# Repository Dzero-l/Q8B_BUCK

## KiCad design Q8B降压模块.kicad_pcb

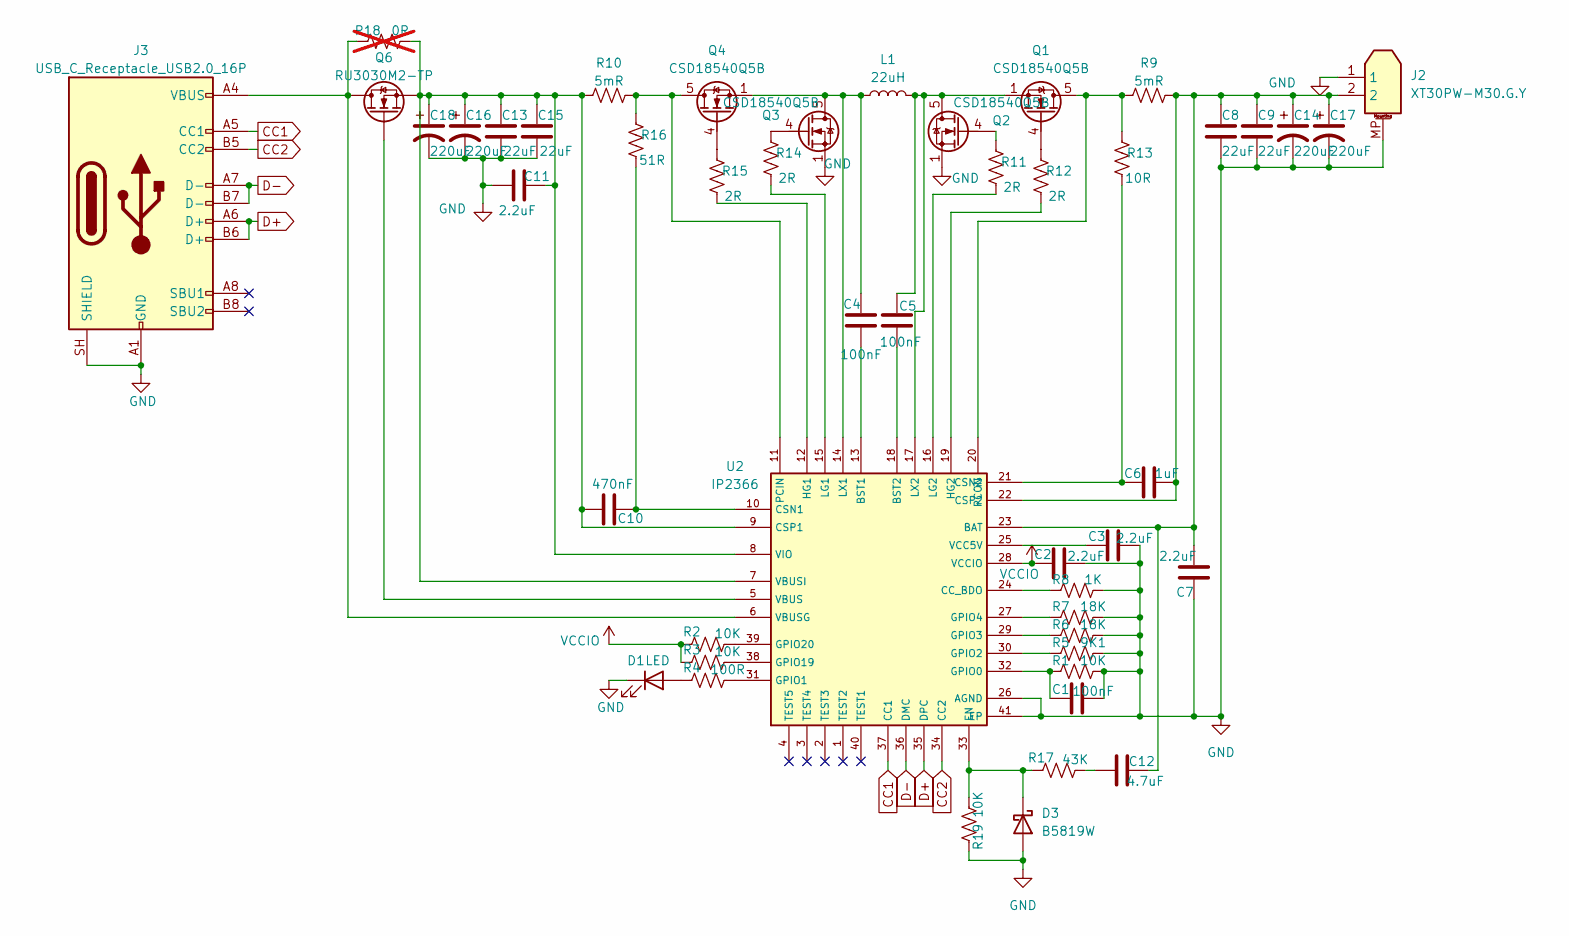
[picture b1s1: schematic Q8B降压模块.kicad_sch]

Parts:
C1, C4, C5: 100nF; C_0603_1608Metric
C2, C3, C7, C11: 2.2uF; C_0603_1608Metric
C6: 1uF; C_0603_1608Metric
C8, C9, C13, C15: 22uF; C_1206_3216Metric
C10: 470nF; C_0603_1608Metric
C12: 4.7uF; C_0805_2012Metric
C14, C16, C17, C18: 220uF; CP_Radial_D8.0mm_P3.50mm
D1: LED; LED_0603_1608Metric
D3: B5819W; D_SOD-123
J2: XT30PW-M30.G.Y; AMASS_XT30PW_M30_G_Y
J3: USB_C_Receptacle_USB2.0_16P; USB_C_Receptacle_GCT_USB4105-xx-A_16P_TopMnt_Horizontal
L1: 22uH; L_APV_APH1770
Q1, Q2, Q3, Q4: CSD18540Q5B; TDSON-8_L5.9-W5.2-P1.27_TPCA8122-Toshiba
Q6: RU3030M2-TP; MPN RU3030M2-TP
R1, R2, R3, R19: 10K; R_0603_1608Metric
R4: 100R; R_0603_1608Metric
R5: 9K1; R_0603_1608Metric
R6, R7: 18K; R_0603_1608Metric
R8: 1K; R_0603_1608Metric
R9, R10: 5mR; R_0612_1632Metric
R11, R12, R14, R15: 2R; R_0603_1608Metric
R13: 10R; R_0603_1608Metric
R16: 51R; R_0603_1608Metric
R17: 43K; R_0603_1608Metric
R18: 0R; C_1206_3216Metric; not fitted
U2: IP2366; QFN-40-5x5mm_P0.4mm_EP3.7mm

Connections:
CC1: J3.A5 (CC1), U2.37 (CC1)
CC2: J3.B5 (CC2), U2.34 (CC2)
D+: J3.A6 (D+), J3.B6 (D+), U2.35 (DPC)
D-: J3.A7 (D-), J3.B7 (D-), U2.36 (DMC)
GND: C1.2, C2.2, C3.2, C7.1, C8.2, C9.2, C11.1, C13.2, C14.2, C15.2, C16.2, C17.2, C18.2, D1.1 (K), D3.2 (A), J2.1, J2.MP, J3.A1 (GND), J3.A12 (GND), J3.B1 (GND), J3.B12 (GND), J3.SH (SHIELD), Q2.1 (S), Q2.2 (S), Q2.3 (S), Q3.1 (S), Q3.2 (S), Q3.3 (S), R1.2, R5.2, R6.2, R7.2, R8.2, R19.1, U2.26 (AGND), U2.41 (EP)
unnamed: C12.1, R17.2
unnamed: D1.2 (A), R4.1
unnamed: D3.1 (K), R17.1, R19.2, U2.33 (EN)
unnamed: Q1.5 (D), R9.1, R13.1, U2.20 (PCON)
unnamed: Q1.4 (G), R12.1
unnamed: C5.2, L1.2, Q1.1 (S), Q1.2 (S), Q1.3 (S), Q2.5 (D), U2.17 (LX2)
unnamed: Q2.4 (G), R11.1
unnamed: C4.2, L1.1, Q3.5 (D), Q4.1 (S), Q4.2 (S), Q4.3 (S), U2.14 (LX1)
unnamed: Q3.4 (G), R14.1
unnamed: Q4.5 (D), R10.2, R16.1, U2.11 (PCIN)
unnamed: Q4.4 (G), R15.1
unnamed: Q6.4 (G), U2.5 (VBUS)
unnamed: C6.2, C7.2, C8.1, C9.1, C12.2, C14.1, C17.1, J2.2, R9.2, U2.22 (CSP2), U2.23 (BAT)
unnamed: C4.1, U2.13 (BST1)
unnamed: C5.1, U2.18 (BST2)
unnamed: R8.1, U2.24 (CC_BDO)
unnamed: C10.2, R16.2, U2.10 (CSN1)
unnamed: C6.1, R13.2, U2.21 (CSN2)
unnamed: C10.1, C11.2, C13.1, C15.1, C16.1, C18.1, Q6.1 (S), Q6.2 (S), Q6.3 (S), R10.1, R18.2, U2.7 (VBUSI), U2.8 (VIO), U2.9 (CSP1)
unnamed: C1.1, R1.1, U2.32 (GPIO0)
unnamed: R4.2, U2.31 (GPIO1)
unnamed: R5.1, U2.30 (GPIO2)
unnamed: R6.1, U2.29 (GPIO3)
unnamed: R7.1, U2.27 (GPIO4)
unnamed: R3.2, U2.38 (GPIO19)
unnamed: R2.2, U2.39 (GPIO20)
unnamed: R15.2, U2.12 (HG1)
unnamed: R12.2, U2.19 (HG2)
unnamed: R14.2, U2.15 (LG1)
unnamed: R11.2, U2.16 (LG2)
unnamed: J3.A4 (VBUS), J3.A9 (VBUS), J3.B4 (VBUS), J3.B9 (VBUS), Q6.5 (D), Q6.6 (D), Q6.7 (D), Q6.8 (D), R18.1, U2.6 (VBUSG)
unnamed: C3.1, U2.25 (VCC5V)
VCCIO: C2.1, R2.1, R3.1, U2.28 (VCCIO)

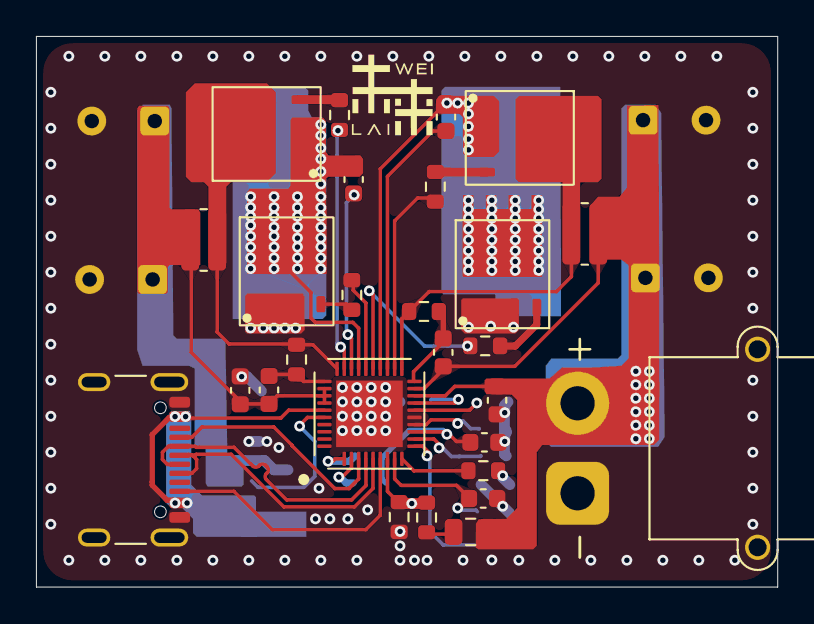
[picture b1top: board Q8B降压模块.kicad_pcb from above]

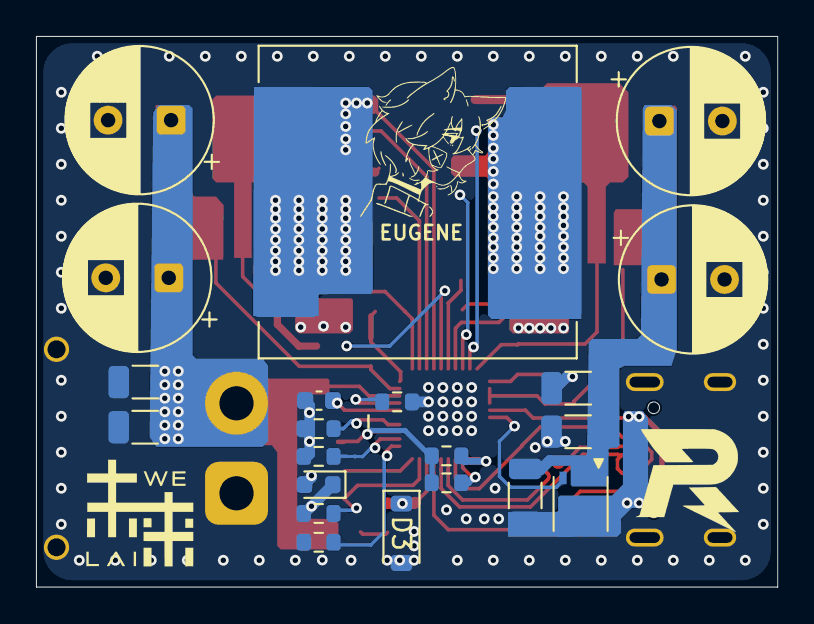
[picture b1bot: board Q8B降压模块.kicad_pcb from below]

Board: 4 copper layers, 41.2 x 30.6 mm, 48 parts (21 on the bottom side), 38 nets.
